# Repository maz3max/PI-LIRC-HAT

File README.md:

# Raspberry PI LIRC HAT #
## Now, you can control everything with an infrared remote with your Raspberry Pi! ##

This an extension PCB for Raspberry PIs with 40 Pins.

Its purpose is to provide a infrared interface compatible with [LIRC](http://www.lirc.org/).

I did my very best to fulfill the [Raspberry Pi HAT specification](https://github.com/raspberrypi/hats).

To build it, you need:
* bravery, soldering skills, linux
* The PCB like in the design file in RaspiIR/RaspiIR.kicad_pcb
* 2x 100nF Ceramic Cap 0603 SMD
* 2x 100uF Electrolytic Cap SMD 6.3mm diameter
* 2x IR-LED: Everlight IR333-A
* 2x IR-LED: Everlight IR333C/H0/L10
* 1x TSOP383xx or AX-1838 IR receiver
* 5x MMBT3904TPMSCT-ND NPN transistor SOT-23
* 1x 24C32 I2C eeprom SOIC-8 or SO-8
* 4x 33R 1W 2512 SMD resistor
* 1x 330R 0603 SMD resistor
* 2x 1k 0603 SMD resistor
* 2x 3.9k 0603 SMD resistor
* 1x Pin-Header 0.1" pitch 2x20 pins (at least 8mm high)

After soldering it all together, you have to generate and write content on the ID eeprom. Its purpose is to load the driver when your Raspberry Pi boots.

To achieve this, follow these steps:

1. compile the tools in pi-lirc-hat/eepromutils with ```make```
2. use ```./eepmake eeprom_settings.txt lircHAT.eep lirc-rpi-overlay.dtbo -c setup-readme-blob``` to compile the eeprom content
3. connect the eeprom to the I2C-Pins of a Raspberry (NOT the ID-SCL, ID-SDA pins)
4. read on how to use eepflash with ```./eepflash.sh -h```
5. use eepflash to write the content to the ID eeprom, e.g.:```./eepflash.sh -w -f=lircHAT.eep -t=24c32 -d=1 -a=50```

After that, you have to install lirc on the Raspberry. This is documented in pi-lirc-hat/eepromutils/setup-readme-blob.

You can also find this in /proc/device-tree/hat/custom_0, because it is included in the eeprom! :D

The design with the 4 IR leds is inspired by [TV-B-Gone](https://learn.adafruit.com/tv-b-gone-kit/overview). The driver overlay is from the [Raspberry Pi Kernel source tree](https://github.com/raspberrypi/linux) with slight modifications. The PCB was designed using [KiCAD](http://kicad-pcb.org/). I used a template for the PCB design which can be found [here](https://github.com/xesscorp/RPi_Hat_Template)

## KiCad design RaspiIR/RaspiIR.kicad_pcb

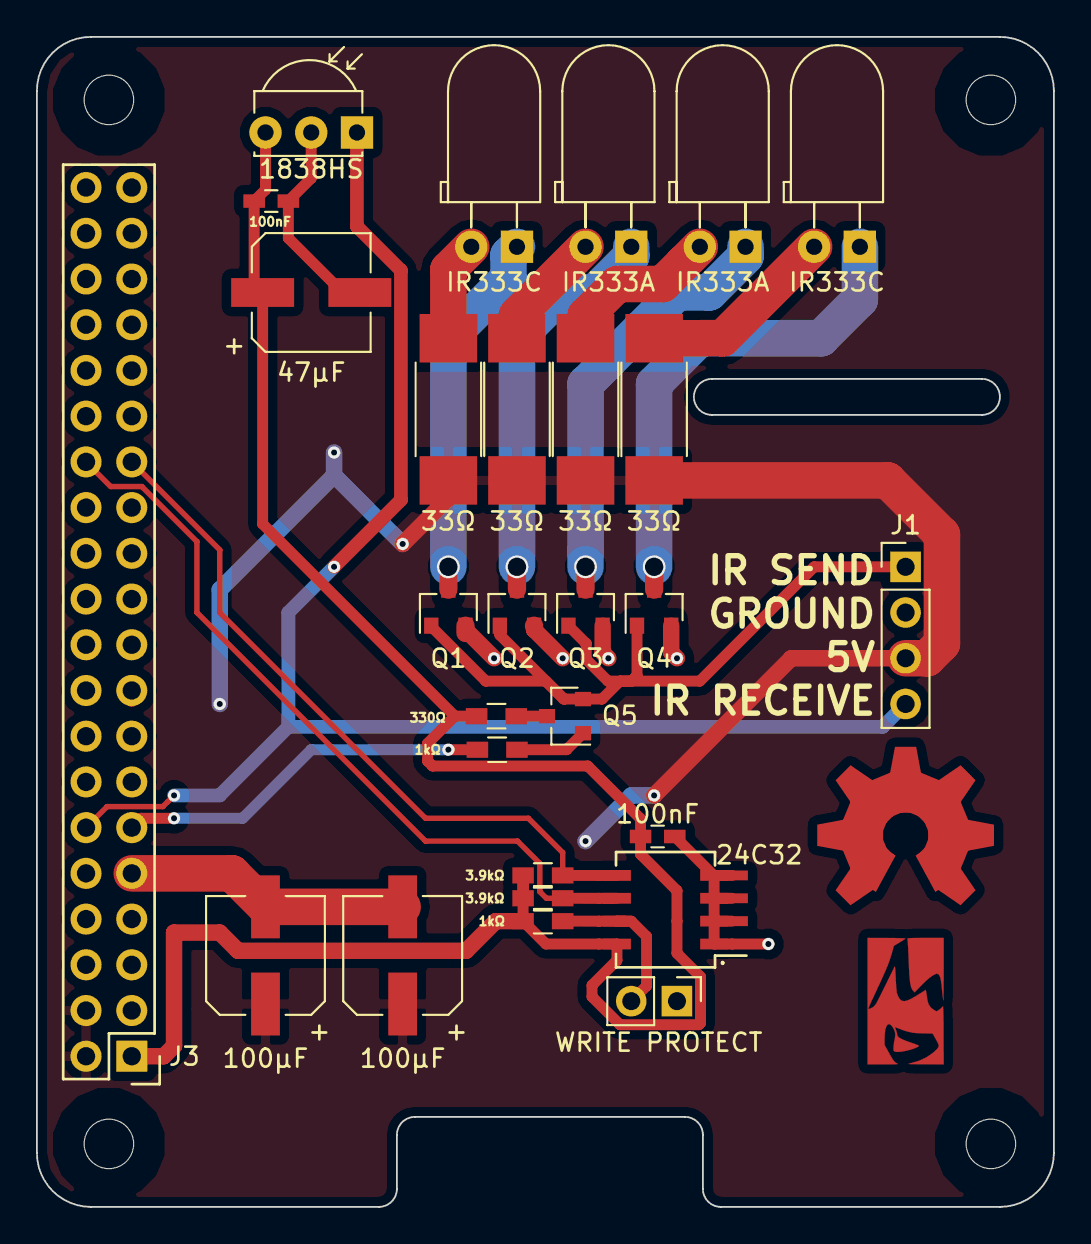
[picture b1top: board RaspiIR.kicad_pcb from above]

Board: 2 copper layers, 56.5 x 65.0 mm, 30 parts (0 on the bottom side), 19 nets.

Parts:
1kΩ, 1kΩ#2: 1k; R_0603_HandSoldering
3.9kΩ, 3.9kΩ#2: 3k9; R_0603_HandSoldering
24C32: CAT24C32WI-GT3; SOIC-8_3.9x4.9mm_Pitch1.27mm
33Ω, 33Ω#2, 33Ω#3, 33Ω#4: 33; R_2512_HandSoldering
47µF, 100µF, 100µF#2: 100u; CP_Elec_6.3x7.7
100nF, 100nF#2: 100n; C_0603_HandSoldering
330Ω: 330; R_0603_HandSoldering
1838HS: TSOP343xx; IRReceiver_Vishay_MOLD-3pin
.: SO-8_5.3x6.2mm_Pitch1.27mm
IR333A, IR333A#2, IR333C, IR333C#2: LED; LED_D5.0mm_Horicontal_O2.54mm
J1: Conn_01x04_Male; Pin_Header_Straight_1x04_Pitch2.54mm
J3: Raspberry_Pi_2_3; Pin_Header_Straight_2x20
OSHW_COPPER_10MM: VAL**; OSHW_COPPER_10MM
Q1, Q2, Q3, Q4, Q5: MMBT3904; SOT-23
WRITE PROTECT: Conn_01x02; Pin_Header_Straight_1x02_Pitch2.54mm

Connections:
+3V3: 1kΩ#2.1, 3.9kΩ.1, 3.9kΩ#2.1, 24C32.8, 47µF.1, 100nF.1, 100nF#2.1, 330Ω.1, 1838HS.3, ..8, J3.1
+5V: 33Ω.2, 33Ω#2.2, 33Ω#3.2, 33Ω#4.2, 100µF.1, 100µF#2.1, J1.3, J3.2, J3.4
GND: 24C32.1, 24C32.2, 24C32.3, 24C32.4, 47µF.2, 100nF.2, 100nF#2.2, 100µF.2, 100µF#2.2, 1838HS.2, ..1, ..2, ..3, ..4, J1.2, J3.6, J3.9, J3.14, J3.20, J3.25, J3.30, J3.34, J3.39, Q1.2, Q2.2, Q3.2, Q4.2, WRITE PROTECT.1
ID_SCL: 3.9kΩ#2.2, 24C32.6, ..6, J3.28
ID_SDA: 3.9kΩ.2, 24C32.5, ..5, J3.27
IR_RECV: 1838HS.1, J1.4, J3.12
IR_SEND: J1.1, Q1.1, Q2.1, Q3.1, Q4.1, Q5.2
IR_SEND_IO: 1kΩ.2, J3.11
unnamed: IR333C.1, Q1.3
unnamed: 33Ω.1, IR333C.2
unnamed: IR333A.1, Q2.3
unnamed: 33Ω#2.1, IR333A.2
unnamed: IR333A#2.1, Q3.3
unnamed: 33Ω#3.1, IR333A#2.2
unnamed: IR333C#2.1, Q4.3
unnamed: 33Ω#4.1, IR333C#2.2
unnamed: 1kΩ#2.2, 24C32.7, ..7, WRITE PROTECT.2
unnamed: 1kΩ.1, Q5.1
unnamed: 330Ω.2, Q5.3
